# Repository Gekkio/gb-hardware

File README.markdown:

# Game Boy -related custom hardware by gekkio
Licensed under Creative Commons Attribution 4.0 International.

Used libraries:

* [gekkio-kicad-libs](https://github.com/Gekkio/gekkio-kicad-libs)
* [kicad-footprints](https://github.com/KiCad/kicad-footprints)
* [kicad-symbols](https://github.com/KiCad/kicad-symbols)

## License violations (a.k.a Naughty List)

All the designs in this repository are licensed very liberally under CC BY 4.0,
so you can modify and/or sell them commercially if you want. There's just one
requirement: **attribution**

Basically it just means this: don't remove the original creator's name from the
design. [Here's the full description about it in CC BY 4.0](https://creativecommons.org/licenses/by/4.0/#deed-conditions)

Known license violations:

- Ferrante Crafts: While it wasn't fully intentional and they've
  apologised, they took my GB-CART32K-A design, altered the silkscreen to
  include their name while removing all mention of mine, and then sold these
  carts to people for profit

[Don't be this meme!](https://knowyourmeme.com/memes/i-made-this)

## GB-BENCH-G1

Test bench board for 1st generation Game Boy CPUs (DMG-CPU, SGB-CPU).

* PCB size: 100x100mm
* PCB thickness: any
* Layer count: 4
* Surface finish: any

## GB-BRK-CART

Breakout Game Boy cartridge.

* PCB size: 51.4x61mm
* PCB thickness: 1.0mm
* Layer count: 2
* Surface finish: ENIG (absolutely *do not* choose HASL)

[GB-BRK-CART v4.0 Mouser project for easy part shopping](http://www.mouser.com/ProjectManager/ProjectDetail.aspx?AccessID=61700168c3)

## GB-BRK-LINK-A

Breakout board for original Game Boy (DMG) link port.

* PCB size: 30x34mm
* PCB thickness: 1.2mm
* Layer count: 2
* Surface finish: any

## GB-BRK-LINK-B

Breakout board for compact link port used in Game Boy Pocket (MGB) and later.

* PCB size: 30x34mm
* PCB thickness: 1.2mm
* Layer count: 2
* Surface finish: any

## GB-BRK-M-XS

Compact male breakout board for the Game Boy cartridge slot.

* PCB size: 51.4x25mm
* PCB thickness: 1.0mm
* Layer count: 2
* Surface finish: ENIG (absolutely *do not* choose HASL)

## GB-BRK-SLOT-A

Breakout board for original Game Boy (DMG) cartridge slot.

* PCB size: 81x80mm
* PCB thickness: 1.2mm
* Layer count: 2
* Surface finish: any

## GB-BRK-SLOT-B

Breakout board for Super Game Boy (SGB) / Super Game Boy 2 (SGB2) cartridge
slot.

* PCB size: 81x80mm
* PCB thickness: 1.2mm
* Layer count: 2
* Surface finish: any

## GB-LIVE32

32 kB ROM-only rapid development cartridge.

* PCB size: 51.4x61mm
* PCB thickness: 1.0mm
* Layer count: 4
* Surface finish: ENIG (absolutely *do not choose HASL*)

[Firmware + software](https://github.com/Gekkio/gb-live32)

[GB-LIVE32 v2.0 Mouser project for easy part shopping](https://www.mouser.com/ProjectManager/ProjectDetail.aspx?AccessID=16281c67ef)

## GB-CART32K-A

Simple ROM-only flash cartridge for 32kx8 PLCC-32 flash (larger chips up to
512kx8 are supported, but only 32k is usable).

* PCB size: 51.4x61mm
* PCB thickness: 1.0mm
* Layer count: 2
* Surface finish: ENIG (absolutely *do not choose HASL*)

## GB-CART256K-A

Simple ROM-only flash cartridge for 128kx8 / 256kx8 PLCC-32 flash.

* PCB size: 51.4x61mm
* PCB thickness: 1.0mm
* Layer count: 2
* Surface finish: ENIG (absolutely *do not choose HASL*)

[Firmware](https://github.com/Gekkio/gb-cart256k-a)

## GB-BRK-CPU-G1

Breakout board for 1st generation Game Boy CPUs (DMG/SGB).

* PCB size: 80x80mm
* PCB thickness: any
* Layer count: 2
* Surface finish: any

## GB-BRK-CPU-G2

Breakout board for 2nd generation Game Boy CPUs (MGB/SGB2).

* PCB size: 80x80mm
* PCB thickness: any
* Layer count: 2
* Surface finish: any

## GB-BRK-TR-A

Breakout board for original Game Boy (DMG) power board transformer.

* PCB size: 24x35mm
* PCB thickness: any
* Layer count: 2
* Surface finish: any

## GB-MBCTEST

Game Boy MBC (Memory Bank Controller) testing cartridge.

* PCB size: 51.4x61mm
* PCB thickness: 1.0mm
* Layer count: 2
* Surface finish: ENIG (absolutely *do not choose HASL*)

## GB-CARTPP-XC

An eXtra Cheap Game Boy cartridge dumper/flasher based on PIC18F45K50.

* PCB size: 80x55mm
* PCB thickness: any (1.0mm recommended)
* Layer count: 2
* Surface finish: any

## GB-CARTPP-DIY

A Game Boy cartridge dumper/flasher based on PIC18F45K50 with DIY-friendly
parts (big and easy to solder).

* PCB size: 100x100mm
* PCB thickness: any
* Layer count: 2
* Surface finish: any

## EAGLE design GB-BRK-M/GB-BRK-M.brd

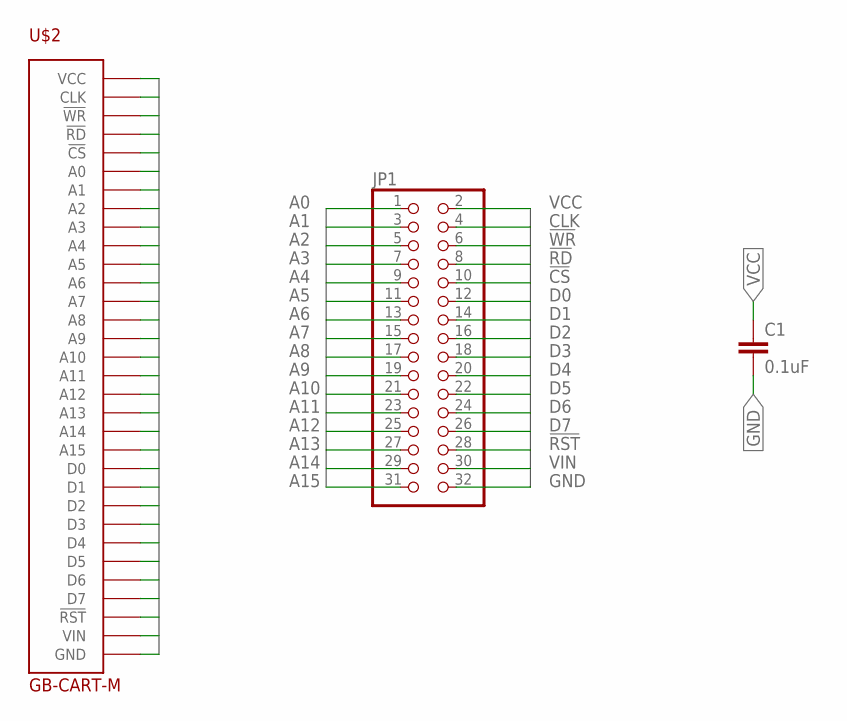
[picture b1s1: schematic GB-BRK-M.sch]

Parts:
C1: 0.1uF; 1206
JP1: PINHD-2X16SMT; 2X16_SMT
U$2: GB-CART-M

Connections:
!CS: JP1.10, U$2.5 (!CS)
!RD: JP1.8, U$2.4 (!RD)
!RST: JP1.28, U$2.30 (!RST)
!WR: JP1.6, U$2.3 (!WR)
A0: JP1.1, U$2.6 (A0)
A1: JP1.3, U$2.7 (A1)
A2: JP1.5, U$2.8 (A2)
A3: JP1.7, U$2.9 (A3)
A4: JP1.9, U$2.10 (A4)
A5: JP1.11, U$2.11 (A5)
A6: JP1.13, U$2.12 (A6)
A7: JP1.15, U$2.13 (A7)
A8: JP1.17, U$2.14 (A8)
A9: JP1.19, U$2.15 (A9)
A10: JP1.21, U$2.16 (A10)
A11: JP1.23, U$2.17 (A11)
A12: JP1.25, U$2.18 (A12)
A13: JP1.27, U$2.19 (A13)
A14: JP1.29, U$2.20 (A14)
A15: JP1.31, U$2.21 (A15)
CLK: JP1.4, U$2.2 (CLK)
D0: JP1.12, U$2.22 (D0)
D1: JP1.14, U$2.23 (D1)
D2: JP1.16, U$2.24 (D2)
D3: JP1.18, U$2.25 (D3)
D4: JP1.20, U$2.26 (D4)
D5: JP1.22, U$2.27 (D5)
D6: JP1.24, U$2.28 (D6)
D7: JP1.26, U$2.29 (D7)
GND: C1.2, JP1.32, U$2.32 (GND)
VCC: C1.1, JP1.2, U$2.1 (VCC)
VIN: JP1.30, U$2.31 (VIN)

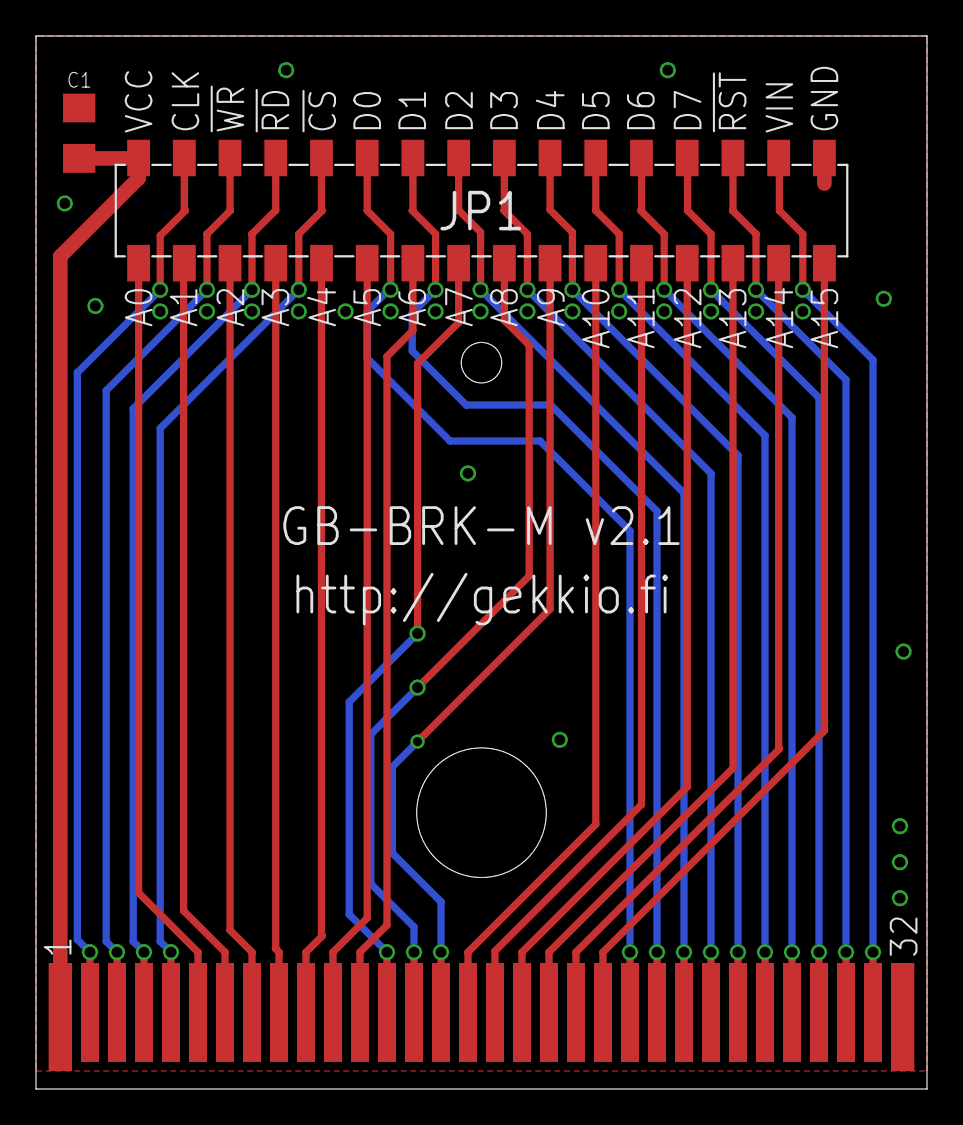
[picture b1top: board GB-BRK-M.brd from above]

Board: 2 copper layers, 49.5 x 58.5 mm, 3 parts (0 on the bottom side), 32 nets.

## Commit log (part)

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2015-08-13 GB-BRK-F v1.0
2015-08-13 Add README
2015-08-13 Add photos to README
2015-08-13 Add TODO
2015-08-13 More TODO
2016-06-16 Ignore some temporary files
2016-06-16 GB-BRK-M v2.1
2016-06-16 GB-BRK-M Board layout, mention ground plane
2016-06-16 GB-BRK-M v2.1 photo
2017-09-03 GB-BRK-M v3.0
2017-09-10 Add GB-BRK-M v3.0 Mouser project link
2017-10-03 GB-BENCH-G1 v1.0
2017-12-12 Use symbols from kicad-library submodule
2018-02-15 GB-BRK-M v3.1
2018-02-15 GB-BRK-M-XS v1.0 + restructuring
2018-02-15 Get rid of old submodule structure
2018-02-15 Oops :O
2018-07-04 GB-BRK-CART v4.0, GB-LIVE32 v2.0
2018-07-09 Minor fixes + add schematic
2018-07-09 Goodbye GB-BRK-M
2018-07-09 More details and fixes
2018-07-09 Oops
2018-07-11 BOM + docs
2018-07-11 More BOM stuff
2018-07-18 Stop recommending bus hold transceivers for GB-LIVE32 boards
2018-07-28 GB-BRK-CPU-G1, GB-BRK-CPU-G2
2019-01-02 GB-BRK-LINK-A, GB-BRK-SLOT-A
2019-01-02 GB-CART2M-A
2019-01-02 Fix schematics broken after library updates
2019-01-02 Goodbye GB-BRK-F
2019-01-05 Update GB-BRK-SLOT-A libs
2019-01-05 Update PCB size and thickness recommendations
2019-06-20 Ignore fp-info-cache
2019-06-20 Add GB-CART2M-A v1.1
2019-06-20 Add GB-BRK-LINK-B v1.0
2019-06-20 Add GB-CART32K-A v1.0
2019-06-20 Optimize with optipng
2019-06-20 Add GB-CART32K-A to README
2020-02-14 Ignore schematic backups
2020-02-14 Update GB-BRK-CPU-G1/G2
2020-02-14 Add GB-BRK-TR-A v1.0
2020-02-14 Rename CART2M -> CART256K, update libs
2020-02-14 Update GB-CART32K-A
2020-02-14 Fix version number in README
2020-02-14 Add firmware/software links
2020-02-14 Add GB-MBCTEST v1.1
2020-02-14 Add GB-BRK-SLOT-B v1.0
2020-02-25 Use a different submodule setup
2020-02-25 Refresh board 3d images
2020-05-17 Set solder mask min width to 0, regenerate gerbers
2020-10-04 Restore old submodule setup
2020-10-04 Add GB-CARTPP-XC v1.2
2020-10-04 Add GB-CARTPP-DIY v1.1
2020-10-04 Remove git submodules
2020-10-04 Squashed 'GB-BENCH-G1/external/gekkio-kicad-libs/' content from commit 11c755d
    git-subtree-dir: GB-BENCH-G1/external/gekkio-kicad-libs
    git-subtree-split: 11c755dfcdc33b887ce2f8f05dc104d8bac43b0a
2020-10-04 Squashed 'GB-BRK-CART/external/gekkio-kicad-libs/' content from commit 68ff78c
    git-subtree-dir: GB-BRK-CART/external/gekkio-kicad-libs
    git-subtree-split: 68ff78c677faf7e9ad431e0bda488bada8557420
2020-10-04 Squashed 'GB-BRK-CART/external/kicad-footprints/' content from commit 93c1f36d
    git-subtree-dir: GB-BRK-CART/external/kicad-footprints
    git-subtree-split: 93c1f36d7492bccb005f4b87ee5bbf2226d03d07
2020-10-04 Squashed 'GB-BRK-CART/external/kicad-symbols/' content from commit db28d85f
    git-subtree-dir: GB-BRK-CART/external/kicad-symbols
    git-subtree-split: db28d85faa814b910e2a16dc6368c1c45187a65d
2020-10-04 Squashed 'GB-BRK-CPU-G1/external/gekkio-kicad-libs/' content from commit edbc4af9
    git-subtree-dir: GB-BRK-CPU-G1/external/gekkio-kicad-libs
    git-subtree-split: edbc4af957fb373c6f8487669a449dabef35f812
2020-10-04 Squashed 'GB-BRK-CPU-G1/external/kicad-footprints/' content from commit db28d85fa
    git-subtree-dir: GB-BRK-CPU-G1/external/kicad-footprints
    git-subtree-split: db28d85faa814b910e2a16dc6368c1c45187a65d
2020-10-04 Squashed 'GB-BRK-CPU-G1/external/kicad-symbols/' content from commit 6127141df
    git-subtree-dir: GB-BRK-CPU-G1/external/kicad-symbols
    git-subtree-split: 6127141dfa6cc83758da58333c4871d682af609c
2020-10-04 Squashed 'GB-BRK-CPU-G2/external/gekkio-kicad-libs/' content from commit edbc4af95
    git-subtree-dir: GB-BRK-CPU-G2/external/gekkio-kicad-libs
    git-subtree-split: edbc4af957fb373c6f8487669a449dabef35f812
2020-10-04 Squashed 'GB-BRK-CPU-G2/external/kicad-footprints/' content from commit ef28214e0
    git-subtree-dir: GB-BRK-CPU-G2/external/kicad-footprints
    git-subtree-split: ef28214e02a0807a5262ed7afe9995762211f28e
2020-10-04 Squashed 'GB-BRK-LINK-A/external/gekkio-kicad-libs/' content from commit ab5ed93c4
    git-subtree-dir: GB-BRK-LINK-A/external/gekkio-kicad-libs
    git-subtree-split: ab5ed93c455c0355b77c4fd9823f606ef7e62302
2020-10-04 Squashed 'GB-BRK-LINK-A/external/kicad-footprints/' content from commit 73119a614
    git-subtree-dir: GB-BRK-LINK-A/external/kicad-footprints
    git-subtree-split: 73119a614f1d35dd87a1b701d7ea77b9698b41d5
2020-10-04 Squashed 'GB-BRK-LINK-A/external/kicad-symbols/' content from commit 6a196c145
    git-subtree-dir: GB-BRK-LINK-A/external/kicad-symbols
    git-subtree-split: 6a196c1457989e8584a95669e2d033e11d83a31d
2020-10-04 Squashed 'GB-BRK-LINK-B/external/gekkio-kicad-libs/' content from commit 8721ad5c9
    git-subtree-dir: GB-BRK-LINK-B/external/gekkio-kicad-libs
    git-subtree-split: 8721ad5c9ea095d1bb754207a810c6bdbffe65f8
2020-10-04 Squashed 'GB-BRK-LINK-B/external/kicad-footprints/' content from commit 6015d7b7b
    git-subtree-dir: GB-BRK-LINK-B/external/kicad-footprints
    git-subtree-split: 6015d7b7b8af2527c2e7a8be9f9f652ea64fbd4d
2020-10-04 Squashed 'GB-BRK-LINK-B/external/kicad-symbols/' content from commit 674655e9f
    git-subtree-dir: GB-BRK-LINK-B/external/kicad-symbols
    git-subtree-split: 674655e9f35b3db56f24f55d6f0971510d0e71c5
2020-10-04 Squashed 'GB-BRK-M-XS/external/gekkio-kicad-libs/' content from commit d15bb29f4
    git-subtree-dir: GB-BRK-M-XS/external/gekkio-kicad-libs
    git-subtree-split: d15bb29f43356d5c0c9f6acf63060d8015be227a
2020-10-04 Squashed 'GB-BRK-M-XS/external/kicad-footprints/' content from commit c42a76b78
    git-subtree-dir: GB-BRK-M-XS/external/kicad-footprints
    git-subtree-split: c42a76b78466583bd626f54cd52a304959612dfd
2020-10-04 Squashed 'GB-BRK-M-XS/external/kicad-symbols/' content from commit 41be9dd93
    git-subtree-dir: GB-BRK-M-XS/external/kicad-symbols
    git-subtree-split: 41be9dd9385a58e37a00dbbb61f88c1f826a0727
2020-10-04 Squashed 'GB-BRK-SLOT-A/external/gekkio-kicad-libs/' content from commit aab0c6a23
    git-subtree-dir: GB-BRK-SLOT-A/external/gekkio-kicad-libs
    git-subtree-split: aab0c6a234ac117c6bacdfbf41116c055d695e5b
2020-10-04 Squashed 'GB-BRK-SLOT-A/external/kicad-footprints/' content from commit ef28214e0
    git-subtree-dir: GB-BRK-SLOT-A/external/kicad-footprints
    git-subtree-split: ef28214e02a0807a5262ed7afe9995762211f28e
2020-10-04 Squashed 'GB-BRK-SLOT-A/external/kicad-symbols/' content from commit 6127141df
    git-subtree-dir: GB-BRK-SLOT-A/external/kicad-symbols
    git-subtree-split: 6127141dfa6cc83758da58333c4871d682af609c
2020-10-04 Squashed 'GB-BRK-SLOT-B/external/gekkio-kicad-libs/' content from commit aab0c6a23
    git-subtree-dir: GB-BRK-SLOT-B/external/gekkio-kicad-libs
    git-subtree-split: aab0c6a234ac117c6bacdfbf41116c055d695e5b
2020-10-04 Squashed 'GB-BRK-SLOT-B/external/kicad-footprints/' content from commit ef28214e0
    git-subtree-dir: GB-BRK-SLOT-B/external/kicad-footprints
    git-subtree-split: ef28214e02a0807a5262ed7afe9995762211f28e
2020-10-04 Squashed 'GB-BRK-SLOT-B/external/kicad-symbols/' content from commit 6127141df
    git-subtree-dir: GB-BRK-SLOT-B/external/kicad-symbols
    git-subtree-split: 6127141dfa6cc83758da58333c4871d682af609c
2020-10-04 Squashed 'GB-BRK-TR-A/external/kicad-footprints/' content from commit ef28214e0
    git-subtree-dir: GB-BRK-TR-A/external/kicad-footprints
    git-subtree-split: ef28214e02a0807a5262ed7afe9995762211f28e
2020-10-04 Squashed 'GB-BRK-TR-A/external/kicad-symbols/' content from commit 6127141df
    git-subtree-dir: GB-BRK-TR-A/external/kicad-symbols
    git-subtree-split: 6127141dfa6cc83758da58333c4871d682af609c
2020-10-04 Squashed 'GB-CART256K-A/external/gekkio-kicad-libs/' content from commit edbc4af95
    git-subtree-dir: GB-CART256K-A/external/gekkio-kicad-libs
    git-subtree-split: edbc4af957fb373c6f8487669a449dabef35f812
2020-10-04 Squashed 'GB-CART256K-A/external/kicad-footprints/' content from commit ef28214e0
    git-subtree-dir: GB-CART256K-A/external/kicad-footprints
    git-subtree-split: ef28214e02a0807a5262ed7afe9995762211f28e
2020-10-04 Squashed 'GB-CART256K-A/external/kicad-symbols/' content from commit 6127141df
    git-subtree-dir: GB-CART256K-A/external/kicad-symbols
    git-subtree-split: 6127141dfa6cc83758da58333c4871d682af609c
2020-10-04 Squashed 'GB-CART32K-A/external/gekkio-kicad-libs/' content from commit edbc4af95
    git-subtree-dir: GB-CART32K-A/external/gekkio-kicad-libs
    git-subtree-split: edbc4af957fb373c6f8487669a449dabef35f812
2020-10-04 Squashed 'GB-CART32K-A/external/kicad-footprints/' content from commit ef28214e0
    git-subtree-dir: GB-CART32K-A/external/kicad-footprints
    git-subtree-split: ef28214e02a0807a5262ed7afe9995762211f28e
2020-10-04 Squashed 'GB-CART32K-A/external/kicad-symbols/' content from commit 6127141df
    git-subtree-dir: GB-CART32K-A/external/kicad-symbols
    git-subtree-split: 6127141dfa6cc83758da58333c4871d682af609c
2020-10-04 Squashed 'GB-CARTPP-DIY/external/gekkio-kicad-libs/' content from commit 2919aa0b7
    git-subtree-dir: GB-CARTPP-DIY/external/gekkio-kicad-libs
    git-subtree-split: 2919aa0b720b1052a1768f17334fa5c2c270bbf9
2020-10-04 Squashed 'GB-CARTPP-DIY/external/kicad-footprints/' content from commit e5d039f23
    git-subtree-dir: GB-CARTPP-DIY/external/kicad-footprints
    git-subtree-split: e5d039f23699e97957c205c386c82ee7433470f3
2020-10-04 Squashed 'GB-CARTPP-DIY/external/kicad-symbols/' content from commit db28d85fa
    git-subtree-dir: GB-CARTPP-DIY/external/kicad-symbols
    git-subtree-split: db28d85faa814b910e2a16dc6368c1c45187a65d
2020-10-04 Squashed 'GB-CARTPP-XC/external/gekkio-kicad-libs/' content from commit 2919aa0b7
    git-subtree-dir: GB-CARTPP-XC/external/gekkio-kicad-libs
    git-subtree-split: 2919aa0b720b1052a1768f17334fa5c2c270bbf9
2020-10-04 Squashed 'GB-CARTPP-XC/external/kicad-footprints/' content from commit e5d039f23
    git-subtree-dir: GB-CARTPP-XC/external/kicad-footprints
    git-subtree-split: e5d039f23699e97957c205c386c82ee7433470f3
2020-10-04 Squashed 'GB-CARTPP-XC/external/kicad-symbols/' content from commit c5e86f1ea
    git-subtree-dir: GB-CARTPP-XC/external/kicad-symbols
    git-subtree-split: c5e86f1ea7a8f0ef7a75cacc0d83d27cf8b718e4
2020-10-04 Squashed 'GB-LIVE32/external/gekkio-kicad-libs/' content from commit 68ff78c67
    git-subtree-dir: GB-LIVE32/external/gekkio-kicad-libs
    git-subtree-split: 68ff78c677faf7e9ad431e0bda488bada8557420
2020-10-04 Squashed 'GB-LIVE32/external/kicad-footprints/' content from commit 93c1f36d7
    git-subtree-dir: GB-LIVE32/external/kicad-footprints
    git-subtree-split: 93c1f36d7492bccb005f4b87ee5bbf2226d03d07
2020-10-04 Squashed 'GB-MBCTEST/external/gekkio-kicad-libs/' content from commit aab0c6a23
    git-subtree-dir: GB-MBCTEST/external/gekkio-kicad-libs
    git-subtree-split: aab0c6a234ac117c6bacdfbf41116c055d695e5b
2020-10-04 Squashed 'GB-MBCTEST/external/kicad-footprints/' content from commit ef28214e0
    git-subtree-dir: GB-MBCTEST/external/kicad-footprints
    git-subtree-split: ef28214e02a0807a5262ed7afe9995762211f28e
2020-10-04 Squashed 'GB-MBCTEST/external/kicad-symbols/' content from commit 6127141df
    git-subtree-dir: GB-MBCTEST/external/kicad-symbols
    git-subtree-split: 6127141dfa6cc83758da58333c4871d682af609c
2021-02-06 Remove broken subtree
2021-02-06 Squashed 'GB-BRK-CART/external/kicad-symbols/' content from commit 68774423
    git-subtree-dir: GB-BRK-CART/external/kicad-symbols
    git-subtree-split: 68774423231dbe8834010941e1d220b286c20071
2021-02-06 Remove broken subtrees
2021-02-06 Squashed 'GB-CARTPP-DIY/external/kicad-symbols/' content from commit c5e86f1e
    git-subtree-dir: GB-CARTPP-DIY/external/kicad-symbols
    git-subtree-split: c5e86f1ea7a8f0ef7a75cacc0d83d27cf8b718e4
2021-02-06 Squashed 'GB-BRK-CPU-G1/external/kicad-footprints/' content from commit ef28214e0
    git-subtree-dir: GB-BRK-CPU-G1/external/kicad-footprints
    git-subtree-split: ef28214e02a0807a5262ed7afe9995762211f28e
2022-05-07 Add naughty list
2022-09-11 Upgrade most projects to KiCad 6
2022-09-11 Rescue GB-BRK-M-XS and convert to KiCad 6
2022-09-11 Rescue GB-BENCH-G1 and convert to KiCad 6
2023-07-20 Upgrade projects to KiCad 7

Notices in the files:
parts and their libraries:
SparkFun-Capacitors: Licensing: Creative Commons ShareAlike 4.0 International - https://creativecommons.org/licenses/by-sa/4.0
